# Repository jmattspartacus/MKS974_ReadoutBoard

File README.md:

This is a simple PCB design for reading out and powering 4 MKS974b transducer gauges through RS232 and/or analog outputs (0-10V scale). It also includes a 12V rail for powering the gauges.

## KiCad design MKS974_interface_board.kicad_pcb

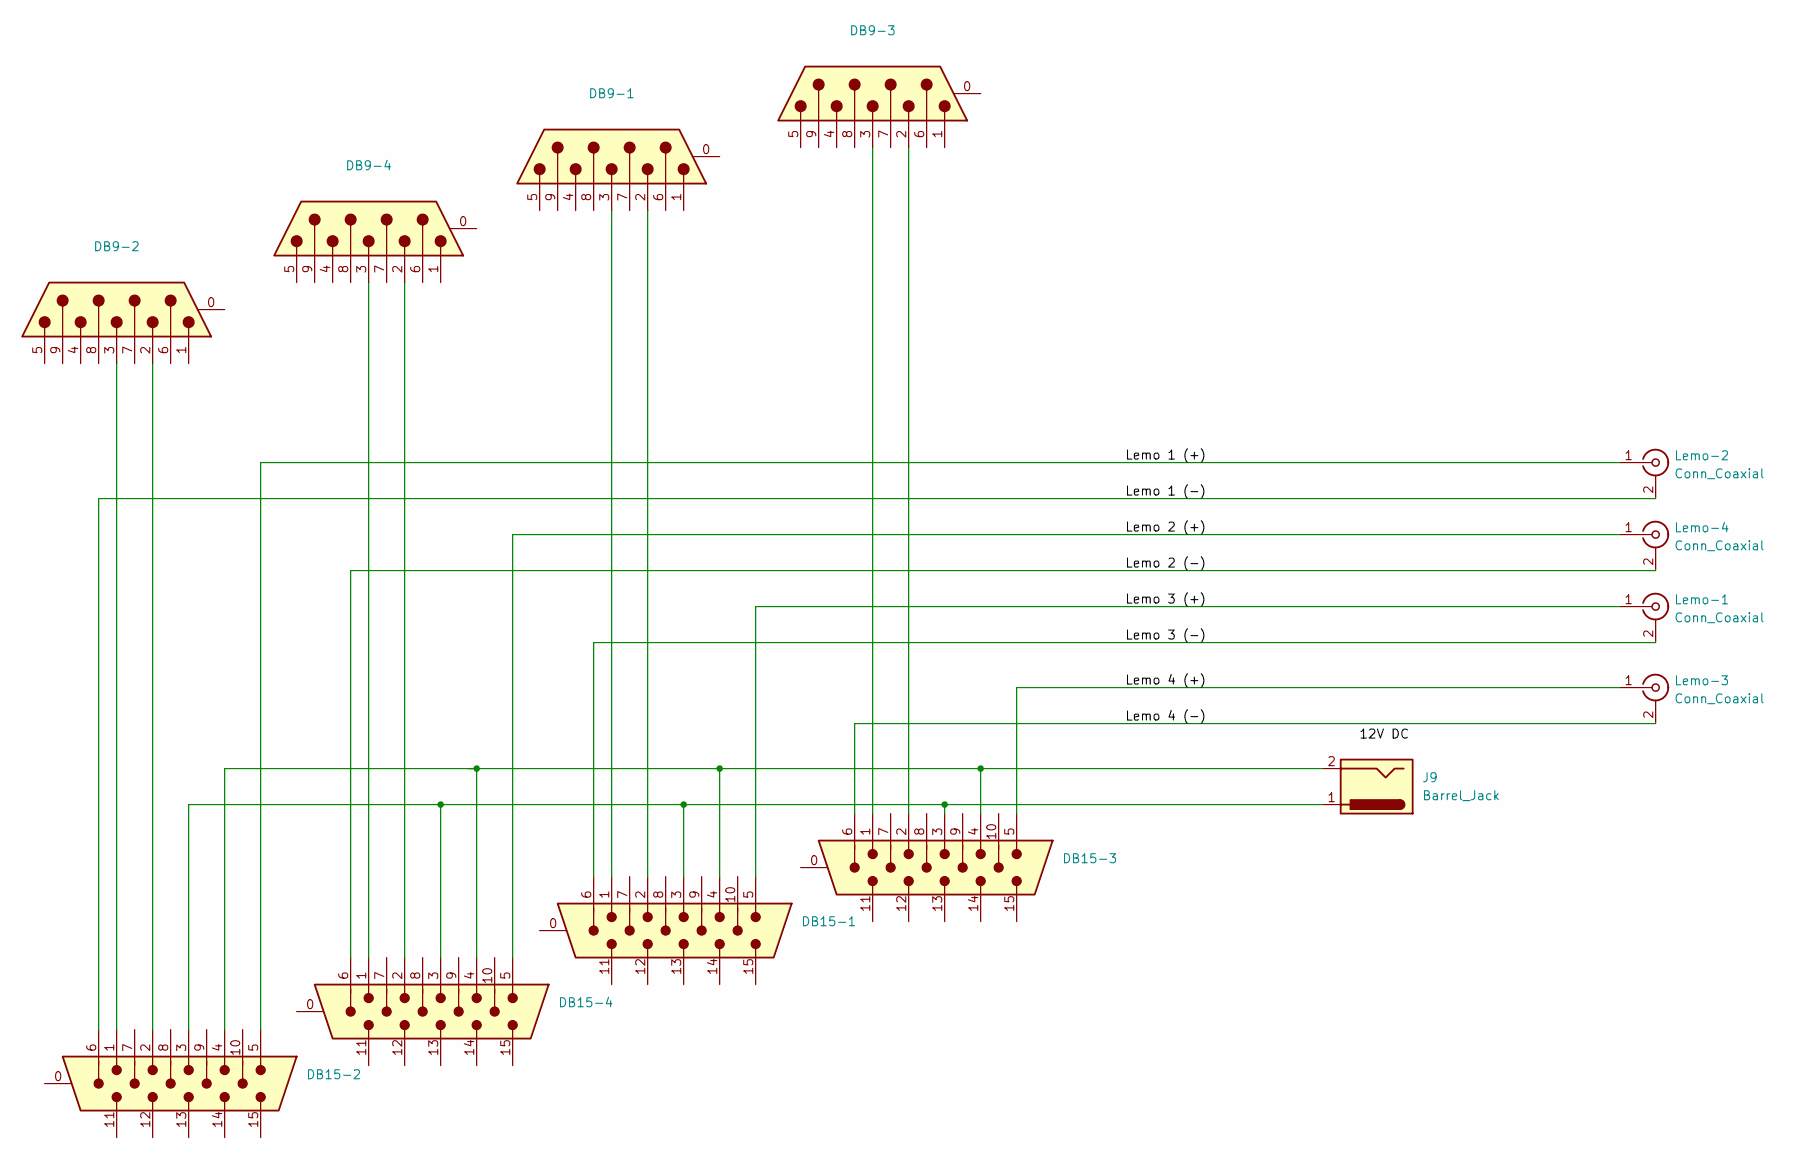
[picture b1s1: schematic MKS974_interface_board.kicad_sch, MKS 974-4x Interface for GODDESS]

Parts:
DB9-1, DB9-2, DB9-3, DB9-4: DB9_Male_MountingHoles; DSUB-9_Receptical_A-DF_09_A_KG-T2S
DB15-1, DB15-2, DB15-3, DB15-4: DB15_Male_HighDensity_MountingHoles; DSUB-15_Male_Horizontal_P2.77x2.84mm_EdgePinOffset9.40mm
J9: Barrel_Jack; BarrelJack_Horizontal
Lemo-1, Lemo-2, Lemo-3, Lemo-4: Conn_Coaxial; LEMO-EPL.00.250.NTN

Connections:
/Lemo 1 (+): DB15-2.5, Lemo-2.1 (In)
/Lemo 1 (-): DB15-2.6, Lemo-2.2 (Ext)
/Lemo 2 (+): DB15-4.5, Lemo-4.1 (In)
/Lemo 2 (-): DB15-4.6, Lemo-4.2 (Ext)
/Lemo 3 (+): DB15-1.5, Lemo-1.1 (In)
/Lemo 3 (-): DB15-1.6, Lemo-1.2 (Ext)
/Lemo 4 (+): DB15-3.5, Lemo-3.1 (In)
/Lemo 4 (-): DB15-3.6, Lemo-3.2 (Ext)
unnamed: DB9-1.3, DB15-1.1
unnamed: DB9-1.2, DB15-1.2
unnamed 10: DB15-1.3, DB15-2.3, DB15-3.3, DB15-4.3, J9.1; also elsewhere on the board
unnamed 11: DB15-1.4, DB15-2.4, DB15-3.4, DB15-4.4, J9.2; also elsewhere on the board
unnamed: DB9-2.3, DB15-2.1
unnamed: DB9-2.2, DB15-2.2
unnamed: DB9-3.3, DB15-3.1
unnamed: DB9-3.2, DB15-3.2
unnamed: DB9-4.3, DB15-4.1
unnamed: DB9-4.2, DB15-4.2

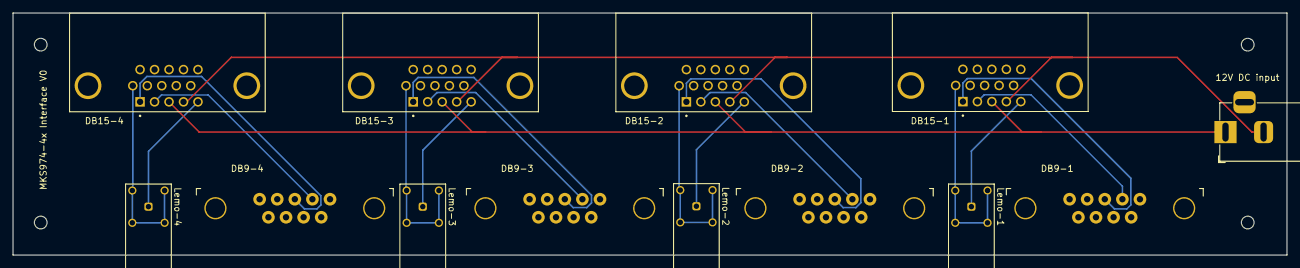
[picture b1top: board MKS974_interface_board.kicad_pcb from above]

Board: 2 copper layers, 200.5 x 38.1 mm, 13 parts (0 on the bottom side), 18 nets.

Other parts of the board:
12V DC input: Barrel_Jack; BarrelJack_Horizontal

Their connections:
unnamed 10: 12V DC input.1; also elsewhere on the board
unnamed 11: 12V DC input.2; also elsewhere on the board

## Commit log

2025-02-15 Initial commit: first pass at design
2025-02-15 Add digikey listing to DB-9 and DB-15 ports
